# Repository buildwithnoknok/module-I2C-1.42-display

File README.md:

# noknok 1.42″ Display Module (I2C)

> **Status:** rev 1.1 boards are **working and in production** (20 pcs, Oct 2026). Firmware
> **v0.7.1** is bench-verified on a production unit: enumeration, drawing, both text paths,
> all four orientations, and brand colours rendering correctly. v0.7.1 hardens the I2C slave
> (DEV-44): the error byte clears when read, and bus glitches no longer re-run old commands.

> ### Rev 1.1 changed the panel control pins — firmware must match
>
> **rev 1.1 swaps D/C and RES** relative to the reworked rev 1.0 boards:
> `PC3 = RES` and `PC4 = D/C` (rev 1.0 had them the other way round). SPI is unaffected.
> Selected by `BOARD_REV_11` in each firmware.
>
> The symptom of getting it wrong is **actively misleading**: lit backlight, visibly running
> MCU, and a completely blank screen — because every command/data decision toggles the panel's
> RESET line while the reset pulse goes to D/C. It looks exactly like a dead panel or a bad
> init table.

<details>
<summary><strong>History: the rev 1.0 mirrored-FPC defect (resolved)</strong></summary>

The first assembled boards (July 2026) had the panel mounted **mirrored**: the
`noknok_ER-TFT1.42-1_13pin_solder_proto` footprint numbered its 13 pads backwards, so board
pad *n* contacted panel pin *14-n*. The panel's **RES** landed on GND (permanent reset), its
**VCC** on the SCK line (never powered), and **LEDA** on a touch-NC pin.

Fixed in the Ecosystem library (commit `cb83a33`) — pad 1 is now on the `+X` end — and
re-fabbed as rev 1.1. Bench boards were rescued by re-soldering the panel rotated 180° in the
plane of the board, which is why rev 1.0 firmware carried a `PANEL_ROTATED_REWORK` switch.

**The lesson worth keeping:** physically compare the pin-1 label printed on the panel's own FPC
against the board's `Pin1` silk marker before ordering. A netlist check cannot catch this
class of error — the schematic was correct all along.

</details>

A modular **1.42-inch colour TFT** display for the noknok ecosystem. A CH32V003 acts as a
local "GPU" — it renders text, icons and graphics to the panel and speaks the noknok I2C
protocol, so the display plugs into the standard JST SH bus like any other module.

## Overview

| | |
|---|---|
| **Panel** | EastRising **ER-TFT1.42-1** — 1.42″ IPS, **80×160**, colour, **NV3022B** controller |
| **MCU** | **CH32V003F4U6** (QFN-20) — local GPU, I2C slave |
| **Bus** | noknok I2C (JST SH 4-pin), 3.3 V |
| **Panel link** | 4-wire SPI (CH32 → NV3022B); interface is fixed, **no IM strapping** |
| **Backlight** | 3 parallel LEDs (~3 V, 45–60 mA) → **MT3540 boost to 4.5 V** + 33 Ω ballast + PWM dimming |
| **FPC** | 13-pin, **0.70 mm pitch, soldered** to the board (PCBWay-assembled) |
| **Board** | **40 × 30 mm** (noknok 4×3 cm standard); 4× M2.5 mounting holes 2.25 mm from each corner; 2× JST-SH on the W + S edges; panel bonded on front, FPC wraps to bottom-side pads |

## Architecture

- **CH32V003 = GPU.** The Pico (Conductor) sends high-level commands ("draw text", "draw
  icon", "blit bitmap"); the CH32 renders to the NV3022B's GRAM over SPI — **framebuffer-less,
  no external RAM**.
- **Assets.** A small default set (one font + common icons, 1bpp, tinted at draw time) lives in
  the CH32's ~12 KB app flash. Anything beyond that is **rendered on the Pico and blitted** as a
  1bpp bitmap (host-supplied assets), so the module is **not limited by its flash** — makers add
  fonts on the Pico side.
- **Standard noknok module behaviour:** dynamic-address enumeration, `GET_VERSION` (0xB1),
  `ENTER_BOOTLOADER` (0xB0), I2C-OTA via the shared CH32V003 bootloader.

## CH32V003F4U6 pinout

| CH32 pin | Function | → Panel |
|---|---|---|
| PC1 / PC2 | I2C SDA / SCL | (noknok bus) |
| PC5 | SPI SCK (via 22 Ω) | SCL/SCK (pin 4) |
| PC6 | SPI MOSI (via 22 Ω) | SDA/MOSI (pin 3) |
| PC3 | **rev 1.1: Reset** / rev 1.0: D/C | **RES (pin 6)** / RS (pin 5) |
| PC4 | **rev 1.1: D/C** / rev 1.0: Reset | **RS (pin 5)** / RES (pin 6) |
| (GND) | CS tied low | CS (pin 7) |
| PD2 | Backlight PWM (TIM1_CH1) | (via 2N7002 + 33 Ω) |
| PD1 | SWIO / flash / status LED | — |
| PD5 / PD6 | UART debug (USART1 TX/RX) | — |
| PD7 | NRST (RC reset) | — |

Panel power: **VCC (pin 10) → 3.3 V** (internal panel power; only VCC + GND needed). Touch
pins (1, 2) and pin 9 = NC.

## Hardware blocks

- **Power/protection:** 3.3V-IN → 10 Ω series + **3.6 V Zener** (clamps below the panel's 3.6 V
  abs-max) → 3.3V-PROT; bulk 10 µF/0.1 µF + MCU & panel decoupling. No on-module I2C pull-ups
  (host-side only).
- **Backlight boost:** MT3540-F23 → **4.5 V** (R1 33 k / R2 12 k), 33 Ω ballast, 2N7002 low-side
  PWM MOSFET on PD2 (100 Ω gate + 100 k pulldown). Boost taps 3.3V-IN (before the series R).
- **Panel:** single VCC, 4-wire SPI. **80×160 is a window in the NV3022B's 132×162 RAM → the
  init sequence needs a column/row offset** (tune at bring-up, like a small ST7735).
- **noknok front-end:** 2× JST SH, 3-pad pogo flash pads (PD1/SWIO), UART debug pads, status
  LED, reset RC. No castellated edges.

## KiCad library

Symbols & footprints live in the **Ecosystem** repo (`electrical/noknok.kicad_sym` + `noknok.pretty/`):

- `noknok_ER-TFT1.42-1` (symbol) + `noknok_ER-TFT1.42-1_13pin_solder` (footprint)
- `noknok_ER-TFT1.42-1_13pin_solder_proto` — prototype variant, **stretched 3.5 mm pads**
  (±0.9 mm FPC-fold slack) + silk alignment rulers; switch back to the production footprint once
  the fold geometry is confirmed.
- `noknok_UART_debug_1x3_pogo`, `noknok_FlashPads_I2C-module_1x3_M2.5`, `noknok_MountingHole`

## Firmware

Source in `firmware/src/`, distributable OTA image in `firmware/bin/`. Linked at `0x1400` (bootloader layout 2) to
run under the shared noknok I2C bootloader; flashed over I2C, not SWD.

### Changelog

Every release from **v0.4.0 onwards must add an entry here before the binary is committed.**
Entries below v0.4.0 were written retrospectively.

#### v0.7.1 — 23 Oct 2026
- **I2C slave hardening (DEV-44).** Three fixes, protocol unchanged:
  - **Error byte is read-to-clear.** A status read returns the last error and resets it to 0, so
    an error belongs to the commands since the previous read. Before, it stayed set until power-off.
  - **A STOP with no address match is ignored.** The ISR copies each finished command into its own
    buffer at STOP and empties the receive buffer. Before, a glitch STOP (for example a host
    `i2c.deinit()`) ran the previous command again, which is where the stray error 4 came from.
  - **A status read can no longer wipe a waiting command.** Because of that copy, an address match
    between a command's STOP and the main loop no longer loses the command.
- Bench (Pi4RFID, production unit): on v0.7.0 an unknown command left error 2 on every later read,
  and a blit followed by a deinit or a bare STOP turned it into error 4. On v0.7.1: error clears
  after one read; 0 of 20 deinit cycles and 0 of 20 bare STOPs give error 4; 0 of 200
  command-then-immediate-read pairs lose the command; a script that ends with a blit + deinit
  leaves error 0 for the next one. `bench_dev41.py` 8/8.

#### v0.7.0 — 1 Oct 2026
- **Runs EastRising's real init sequence, including the gamma table** (`VENDOR_INIT`), ported
  from the ER-TFT1.42-1 8051 tutorial on buydisplay.com. **This fixes brand colours**:
  `#8B00F3` renders as actual purple. Previously, with no gamma table, the controller ran its
  power-on curve, which mis-maps mid-level codes — purple (R 54.8% / B 96.8%) came out blue
  because the red was flattened while the near-rail blue passed through.
- **Why the July vendor-table attempt killed four panels, finally understood.** Vendor
  registers sit behind a locked page: EastRising unlocks with `0xFF,0xA5`, but the generic
  Espressif `esp_lcd_nv3022b` table we tried used `0xFD,0x06,0x08`. Wrong key, so every
  vendor write hit a locked page — and the gamma block is written through `0x2A/0x2B/0x2C`,
  which *outside* the unlocked page are CASET/RASET/**RAMWR**. Doing that blind sets a
  nonsense address window and dumps 64 bytes into GRAM.
- MADCTL is now **init-dependent**: the vendor sets scan direction with the vendor register
  `0xC3 = 0x11` (ss/gs). Both tables are bench-measured, not derived:

  | rot | vendor init | minimal init |
  |---|---|---|
  | 0 portrait | `0xC0` | `0x40` |
  | 1 landscape (default) | `0xA0` | `0x20` |
  | 2 portrait flipped | `0x00` | `0x80` |
  | 3 landscape flipped | `0x60` | `0xE0` |

- COLMOD is the vendor's `0x55` (was `0x05`). The minimal init survives under `#else` —
  one define reverts everything.
- Vendor code independently confirms two values found empirically in July: `LCD_SetPos()`
  uses `x0 + 24` (our GRAM offset) and the init contains `INVON 0x21`.

#### v0.6.0 — 1 Oct 2026
- **rev 1.1 pin mapping** (`BOARD_REV_11`): `PC3 = RES`, `PC4 = D/C`. Neither this
  firmware nor the bring-up could drive a rev 1.1 board before this.
- **Default orientation is now landscape** (160×80). Named `ROT_*` constants plus
  `DEFAULT_ROTATION`, and a single `gpu_set_rotation()` helper serving both the boot
  default and `SET_ROTATION` so the two cannot drift apart.
- **Fixed: `gpu_window()` ignored the runtime GRAM offsets**, using the compile-time
  constants instead. `g_xoff`/`g_yoff` were written by `SET_ROTATION` and
  `SET_ORIENT` and never read, so the rotation API changed MADCTL and geometry but
  silently dropped the offsets.
- **Fixed: portrait MADCTL was `0x00`, which renders text mirrored.** A symmetric border
  cannot reveal that — only text can, which is why it survived the original bring-up.
- **All four rotations bench-verified**, retiring the `offsets for anything other than
  rotation 0 are guesses` caveat. The effective RAM is **128** wide (offset 24 is
  symmetric); the blurb's 132×162 is the NV3022B maximum, not this panel's mapping.
- `draw_splash()` is centred on the live geometry; it previously drew at y=60..98, off the
  bottom of an 80 px-tall landscape panel.

#### v0.5.0 — 11 Sep 2026
- Relinked at the `0x1400` flash offset (bootloader **layout 2**: 1 KB stage-0 + 4 KB stage-1 below the app; was `0x1000`). Firmware behaviour unchanged. **Not compatible with the legacy monolithic bootloader or a layout-1 stage-1** — such a module gets stage-0 + stage-1 v1.1.0 over SWD first, then this app over I²C. See [module-I2C-bootloader](https://github.com/buildwithnoknok/module-I2C-bootloader).

#### v0.4.0 — 11 Sep 2026
- Runs the independent watchdog (~2 s, kicked every main-loop pass) and writes `0` to `0x200007F8` the moment its I²C address is assigned — the app-health handshake with the stage-1 bootloader. Stage-1 counts watchdog resets and parks the module (error 7, rescued by the Conductor by UID) after three in a row, instead of booting a broken app forever. Contract: [Ecosystem / software / bootloader-update.md §3](https://github.com/buildwithnoknok/Ecosystem/blob/main/software/bootloader-update.md). No protocol or command change. The watchdog is also kicked inside the backlight ramp (the one blocking loop).

#### v0.3.0 — 23 Jul 2026
- `SET_ROTATION` (0x11) and `SET_ORIENT` (0x14). Panel geometry and GRAM offsets became
  **runtime state** rather than compile-time constants, so clipping, `GET_INFO` and the blit
  bounds all follow the current orientation.
- `SET_ORIENT` is a bench calibrator taking a raw MADCTL plus offsets: the MADCTL values are
  certain but the offsets for any rotation other than 0 are unknown, because the controller's
  true GRAM width is undocumented.
- Version bumped purely so the orientation build is distinguishable from v0.2.0 over
  `GET_VERSION` — v0.2.0 shipped twice with different command sets, which was a mistake.

#### v0.2.0 — 23 Jul 2026
- Built-in **8×8 monospace font**, ASCII 0x20–0x7E (760 bytes), generated from the
  public-domain `dhepper/font8x8`. Bit order is LSB-first (bit 0 = leftmost).
- `DRAW_TEXT` (0x03) with integer scale 1–8 → native heights 8/16/24/32/40/48/56/64.
- `BLIT_BEGIN` (0x05) / `BLIT_DATA` (0x06): 1bpp host-rendered assets streamed in ≤64-byte
  chunks and expanded to RGB565 on arrival — the CH32V003 cannot buffer a bitmap in 2 KB.
- Style-byte layout aligned with `noknok.py`; transparent blit fixed (it previously streamed
  pixels without opening a window).
- `GET_INFO` corrected to report 1 built-in font.

#### v0.1.0 — 23 Jul 2026
- First real module firmware. Enumeration as **MODULE_TYPE 0x05**, `GET_VERSION` (0xB1),
  `ENTER_BOOTLOADER` (0xB0), `GET_INFO` (0x15).
- GPU: hardware SPI, minimal DCS init, `INVON`, GRAM offset (24, 0), clipped `CLEAR` and
  `FILL_RECT`, backlight PWM with a soft-start ramp, boot splash.
- Command processor snapshots `rx_buf` before drawing — a full-screen fill is ~35 ms of SPI and
  the I2C ISR can land the next command mid-draw.

### Known gaps

- The status LED is not driven — PD1/SWIO does not work (Jira DEV-20).
- Icons, images and screen layouts are designed in the browser with the
  [noknok Display Planner](https://buildwithnoknok.github.io/display-planner/) — it previews the
  panel pixel-for-pixel (including this firmware's 8×8 font and the landscape boot orientation)
  and exports ready-to-paste `noknok.py` code
  ([source](https://github.com/buildwithnoknok/Ecosystem/tree/main/software/display-planner),
  [how-to](https://buildwithnoknok.github.io/display-planner-guide/)).
- Icons and a second (larger) font are not implemented in firmware, and no longer need to be:
  since `noknok.py` v1.9 (DEV-41) icons, images, `print()` and named regions are rendered
  on the Pico and streamed over the existing 1bpp `BLIT` path. `DRAW_ICON` (0x04) is
  reserved/unused.
- The **bring-up** firmware (`firmware/bringup/`) still runs the minimal init, so brand
  colours render wrong there. That is fine for its job (liveness, offsets, wiring) but do not
  judge colour with it — use the module firmware.
- `panel_flood.c` keeps the **generic Espressif init table purely as a documented dead end**.
  It is missing the `0xFF,0xA5` unlock, so it cannot work on this panel. Do not revive it.

Resolved in v0.6.0 / v0.7.0: mirrored text, unverified rotation offsets, the rev 1.1 pin
mapping, and brand colours rendering blue.

## Status / next steps

- [x] Schematic, PCB layout, BOM, fabrication — rev 1.1 in production (20 pcs)
- [x] Bring-up: pin-1/fold/offset verified; GRAM offset (24,0), confirmed against the vendor's
      own `LCD_SetPos()`
- [x] Firmware v0.7.0 — bench-verified end to end on a production unit, vendor gamma, all four
      orientations, landscape default
- [ ] **DEV-44** I2C slave robustness hardening (the one real open firmware item)
- [ ] Re-check `BOARD_REV_11` and the MADCTL table on the next panel lot — both are
      hardware-specific and neither is guaranteed across a lot change
- [ ] Consider `-Wundef` in the ch32fun builds: a `#define` placed after the `#if` that
      tests it evaluates to 0 silently, which cost real bench time in this repo twice

## Hardware

KiCad schematic in `hardware/` (to be added). Panel: [ER-TFT1.42-1 datasheet](https://www.buydisplay.com)
· Controller: NV3022B.

## License

Follows the noknok open standard once public — firmware **MIT**, hardware **CC BY-SA 4.0** — with a
link to the central safety & liability page. (Repo is private during development; Christopher sets
visibility + adds LICENSE files at the public rollout.)

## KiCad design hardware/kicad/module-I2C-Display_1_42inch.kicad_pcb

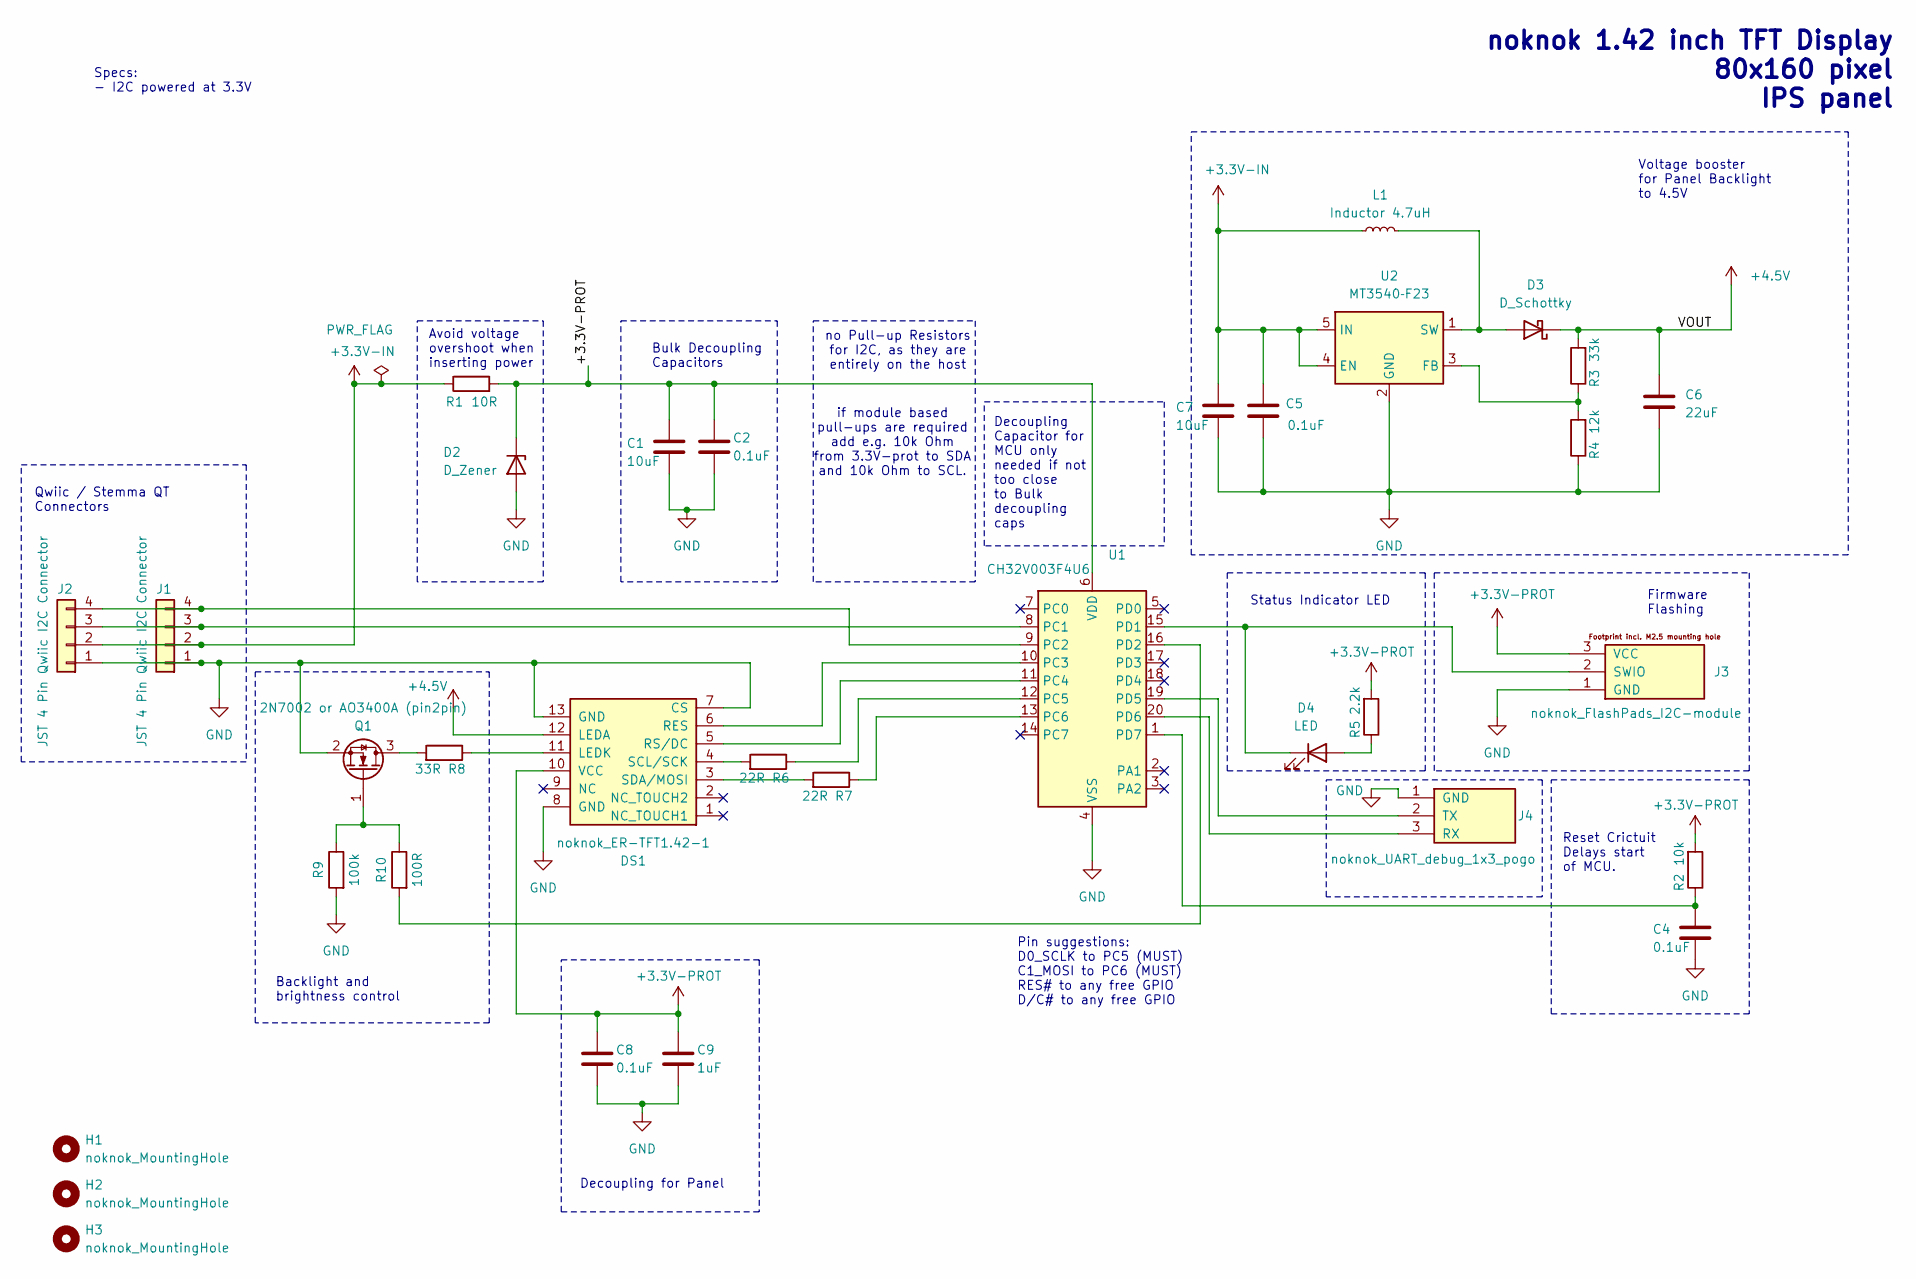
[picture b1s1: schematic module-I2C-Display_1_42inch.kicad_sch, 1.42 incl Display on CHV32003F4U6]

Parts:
C1, C7: 10uF; C_0603_1608Metric
C2, C4, C5, C8: 0.1uF; C_0603_1608Metric
C6: 22uF; C_0603_1608Metric
C9: 1uF; C_0603_1608Metric
D2: D_Zener; D_SOD-323
D3: D_Schottky; D_SOD-323
D4: LED; LED_0603_1608Metric
DS1: noknok_ER-TFT1.42-1; noknok_ER-TFT1.42-1_13pin_solder_proto
H1, H2, H3: noknok_MountingHole; noknok_MountingHole_2.5mm_M2.5
J1, J2: JST 4 Pin Qwiic I2C Connector; JST_SH_SM04B-SRSS-TB_1x04-1MP_P1.00mm_Horizontal
J3: noknok_FlashPads_I2C-module; noknok_FlashPads_I2C-module_1x3_M2.5
J4: noknok_UART_debug_1x3_pogo
L1: Inductor 4.7uH; L_Changjiang_FTC252010S
Q1: 2N7002 or AO3400A (pin2pin); SOT-23
R1: 10R; R_0603_1608Metric
R2: 10k; R_0603_1608Metric
R3: 33k; R_0603_1608Metric
R4: 12k; R_0603_1608Metric
R5: 2.2k; R_0603_1608Metric
R6, R7: 22R; R_0603_1608Metric
R8: 33R; R_0603_1608Metric
R9: 100k; R_0603_1608Metric
R10: 100R; R_0603_1608Metric
U1: CH32V003F4U6; QFN-20-1EP_3x3mm_P0.4mm_EP1.65x1.65mm
U2: MT3540‑F23; SOT-23-5

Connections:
+3.3V-IN: C5.1, C7.1, J1.2, J2.2, L1.1, R1.1, U2.4 (EN), U2.5 (IN)
+3.3V-PROT: C1.1, C2.1, C8.1, C9.1, D2.1 (K), DS1.10 (VCC), J3.3 (VCC), R1.2, R2.2, R5.2, U1.6 (VDD)
+4.5V: C6.1, D3.1 (K), DS1.12 (LEDA), R3.2
GND: C1.2, C2.2, C4.2, C5.2, C6.2, C7.2, C8.2, C9.2, D2.2 (A), DS1.7 (CS), DS1.8 (GND), DS1.13 (GND), J1.1, J2.1, J3.1 (GND), J4.1 (GND), Q1.2 (S), R4.1, R9.2, U1.4 (VSS), U1.21 (VSS), U2.2 (GND)
unnamed: D3.2 (A), L1.2, U2.1 (SW)
unnamed: D4.2 (A), R5.1
unnamed: D4.1 (K), J3.2 (SWIO), U1.15 (PD1)
unnamed: DS1.11 (LEDK), R8.1
unnamed: DS1.6 (RES), U1.10 (PC3)
unnamed: DS1.5 (RS/DC), U1.11 (PC4)
unnamed: DS1.4 (SCL/SCK), R6.2
unnamed: DS1.3 (SDA/MOSI), R7.2
unnamed: J1.3, J2.3, U1.8 (PC1)
unnamed: J1.4, J2.4, U1.9 (PC2)
unnamed: J4.3 (RX), U1.20 (PD6)
unnamed: J4.2 (TX), U1.19 (PD5)
unnamed: Q1.3 (D), R8.2
unnamed: Q1.1 (G), R9.1, R10.1
unnamed: R6.1, U1.12 (PC5)
unnamed: R7.1, U1.13 (PC6)
unnamed: R10.2, U1.16 (PD2)
unnamed: C4.1, R2.1, U1.1 (PD7)
unnamed: R3.1, R4.2, U2.3 (FB)

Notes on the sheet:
Voltage booster for Panel Backlight to 4.5V
if module based pull-ups are required add e.g. 10k Ohm from 3.3V-prot to SDA and 10k Ohm to SCL.
Decoupling Capacitor for MCU only needed if not too close to Bulk decoupling caps
Avoid voltage overshoot when inserting power
Specs: - I2C powered at 3.3V
noknok 1.42 inch TFT Display 80x160 pixel IPS panel
Pin suggestions: D0_SCLK to PC5 (MUST) C1_MOSI to PC6 (MUST) RES# to any free GPIO D/C# to any free GPIO
no Pull-up Resistors for I2C, as they are entirely on the host
Decoupling for Panel
Reset Crictuit Delays start of MCU.
Status Indicator LED
Firmware Flashing
Backlight and brightness control
Qwiic / Stemma QT Connectors
Bulk Decoupling Capacitors

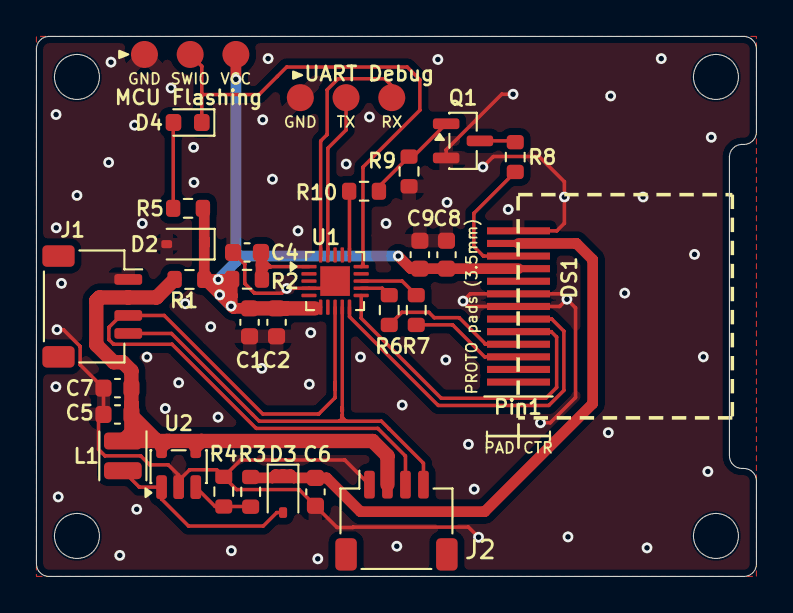
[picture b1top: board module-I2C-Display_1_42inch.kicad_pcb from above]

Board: 2 copper layers, 40.0 x 30.0 mm, 33 parts (0 on the bottom side), 23 nets.

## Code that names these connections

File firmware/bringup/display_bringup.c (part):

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 *   directly (NOT under the noknok I2C bootloader, NOT an I2C module yet).
 *   Its only job is to answer the three unknowns on a brand-new board:
 *
 *     1. Does the backlight chain work?  (MT3540 boost → 33R → 2N7002 on PD2)
 *     2. Does the SPI link to the NV3022B work at all?
 *     3. What are the COLUMN/ROW OFFSETS of the 80x160 visible window inside
 *        the controller's larger internal GRAM?  ← the real unknown
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 *   (enumeration + GPU command set + bootloader relink at 0x1000).
 *
 * ── Hardware (verified against the schematic netlist, Jul 2026) ───────────
 *   PC5  SPI1_SCK   → 22R → panel SCL/SCK (pin 4)
 *   PC6  SPI1_MOSI  → 22R → panel SDA/MOSI (pin 3)
 *   PC3  rev1.1 → panel RES (pin 6) / rev1.0 → panel RS (pin 5)
 *   PC4  rev1.1 → panel RS (pin 5) / rev1.0 → panel RES (pin 6)  (BOARD_REV_11)
 *   ---  CS tied to GND on the board (panel always selected)
 *   PD2  Backlight PWM (TIM1_CH1) → 100R → 2N7002 gate (low-side switch)
 *   PD1  Status LED (ACTIVE LOW: 3V3 → 2.2k → LED → PD1) + SWIO/flash pad
 *   PC1/PC2  I2C — unused in this bring-up build
 *
 * ── How to use it at the bench ────────────────────────────────────────────
 *   PHASE 1 (~4 s):  panel held in reset, backlight ramps 0 → 100 % → 0.
 *                    You should see the screen glow evenly (dark, no image).
 *                    If nothing glows: boost / 33R / 2N7002 / PD2 problem.
 *                    Status LED = slow heartbeat.
 *
 *   PHASE 2 (loop):  the panel is initialised, then the firmware CYCLES
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 *     · the init table is a generic NV3022B vendor sequence; the panel may
 *       need EastRising's own. Grab the ER-TFT1.42-1 demo code from
 *       buydisplay.com and replace nv3022b_init_seq[] wholesale.
 *     · D/C/RES swapped or not driven — scope PC3/PC4
 */

#include "ch32fun.h"
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/* ---- Board revision: D/C and RES are SWAPPED between revisions -----------
 * Bench-found 1 Oct 2026 on the first small-batch production unit.
 *
 *   rev 1.0 (reworked bench board)            PC3 = D/C,  PC4 = RES
 *   rev 1.1 (production, corrected footprint) PC3 = RES,  PC4 = D/C
 *
 * Verified against hardware/kicad/module-I2C-Display_1_42inch.kicad_pcb:
 * U1 pad 10 (PC3) -> Net-(DS1-RES), U1 pad 11 (PC4) -> Net-(DS1-RS/DC).
 * SPI is unaffected: PC5 -> R6 -> SCL/SCK, PC6 -> R7 -> SDA/MOSI, which is
 * what SPI1's fixed alternate function requires. CS is still tied to GND.
 *
 * SYMPTOM IF WRONG: lit backlight, MCU visibly alive, screen totally blank -
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#define DC_HIGH()   (GPIOC->BSHR = (1u << PIN_DC))
#define RES_LOW()   (GPIOC->BCR  = (1u << PIN_RES))
#define RES_HIGH()  (GPIOC->BSHR = (1u << PIN_RES))
#define LED_ON()    (GPIOD->BCR  = (1u << 1))    /* PD1 active LOW           */
#define LED_OFF()   (GPIOD->BSHR = (1u << 1))

/* ═══════════════════════════════════════════════════════════════════════════
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}

/* ═══════════════════════════════════════════════════════════════════════════
 * BACKLIGHT — TIM1_CH1 on PD2, hardware PWM
 * ═══════════════════════════════════════════════════════════════════════════ */

static void backlight_init(void)
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     *   0xB = alternate-function push-pull, 50 MHz  (SPI pins) */
    GPIOC->CFGLR &= ~(0xFu << (4 * 3) | 0xFu << (4 * 4)
                    | 0xFu << (4 * 5) | 0xFu << (4 * 6));
    GPIOC->CFGLR |=  (0x1u << (4 * 3))    /* PC3 D/C   output PP              */
                  |  (0x1u << (4 * 4))    /* PC4 RES   output PP              */
                  |  (0xBu << (4 * 5))    /* PC5 SCK   AF PP                  */
                  |  (0xBu << (4 * 6));   /* PC6 MOSI  AF PP                  */

    /* GPIOD — PD1 status LED (output PP), PD2 backlight (AF PP for TIM1_CH1,
     * default mapping, no remap needed). */
    GPIOD->CFGLR &= ~(0xFu << (4 * 1) | 0xFu << (4 * 2));
    GPIOD->CFGLR |=  (0x1u << (4 * 1))
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
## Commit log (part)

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2026-06-30 Add README for the 1.42in I2C display module
    CH32V003 GPU + ER-TFT1.42-1 80x160 IPS panel (NV3022B), 4-wire SPI,
    MT3540 backlight boost. Overview, pinout, architecture, KiCad lib refs,
    firmware TODO and next steps. In development (schematic done, pre-prototype).
2026-06-30 Add KiCad hardware (schematic) + LICENSE files + .gitignore
    hardware/ = KiCad project (schematic). LICENSE = MIT (firmware),
    LICENSE-hardware = CC BY-SA 4.0 (hardware), per the noknok open standard.

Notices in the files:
firmware/bringup/display_bringup.c:
SPDX-License-Identifier: MIT
SPDX-FileCopyrightText: 2026 noknok / Christopher Houben
